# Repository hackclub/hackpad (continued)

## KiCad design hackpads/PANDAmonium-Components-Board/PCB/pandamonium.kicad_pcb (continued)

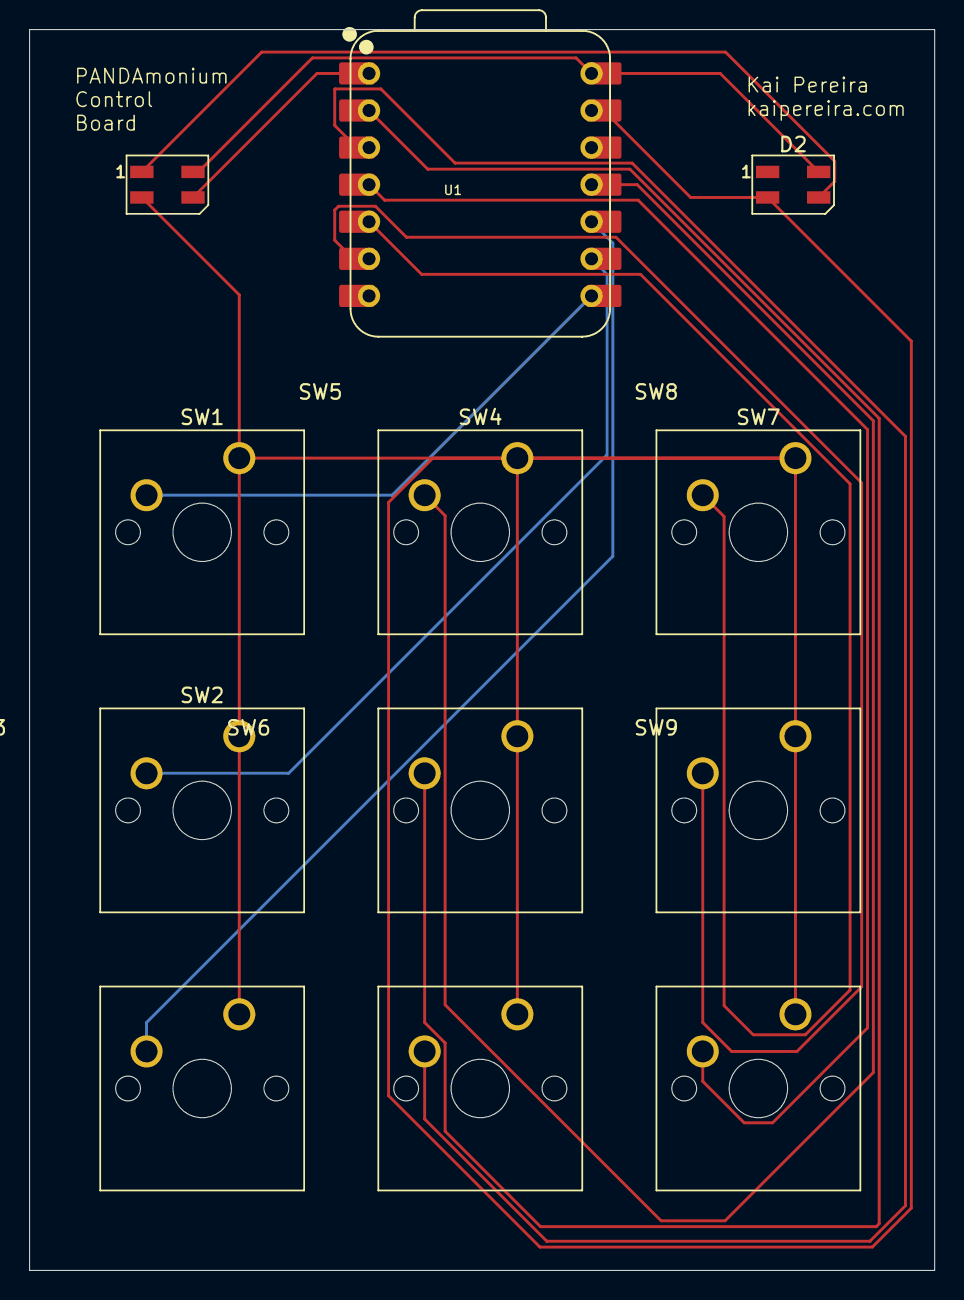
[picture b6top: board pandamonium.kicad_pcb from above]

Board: 2 copper layers, 62.0 x 85.0 mm, 12 parts (0 on the bottom side), 13 nets.

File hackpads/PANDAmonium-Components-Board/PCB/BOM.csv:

"Id";"Designator";"Footprint";"Quantity";"Designation";"Supplier and ref";
1;"SW6,SW9,SW1,SW4,SW7,SW2,SW5,SW3,SW8";"SW_Cherry_MX_1.00u_PCB";9;"SW_Push";;;
2;"D1,D2";"LED_SK6812MINI_PLCC4_3.5x3.5mm_P1.75mm";2;"SK6812MINI";;;
3;"U1";"XIAO-RP2040-DIP";1;"XIAO-RP2040-DIP";;;

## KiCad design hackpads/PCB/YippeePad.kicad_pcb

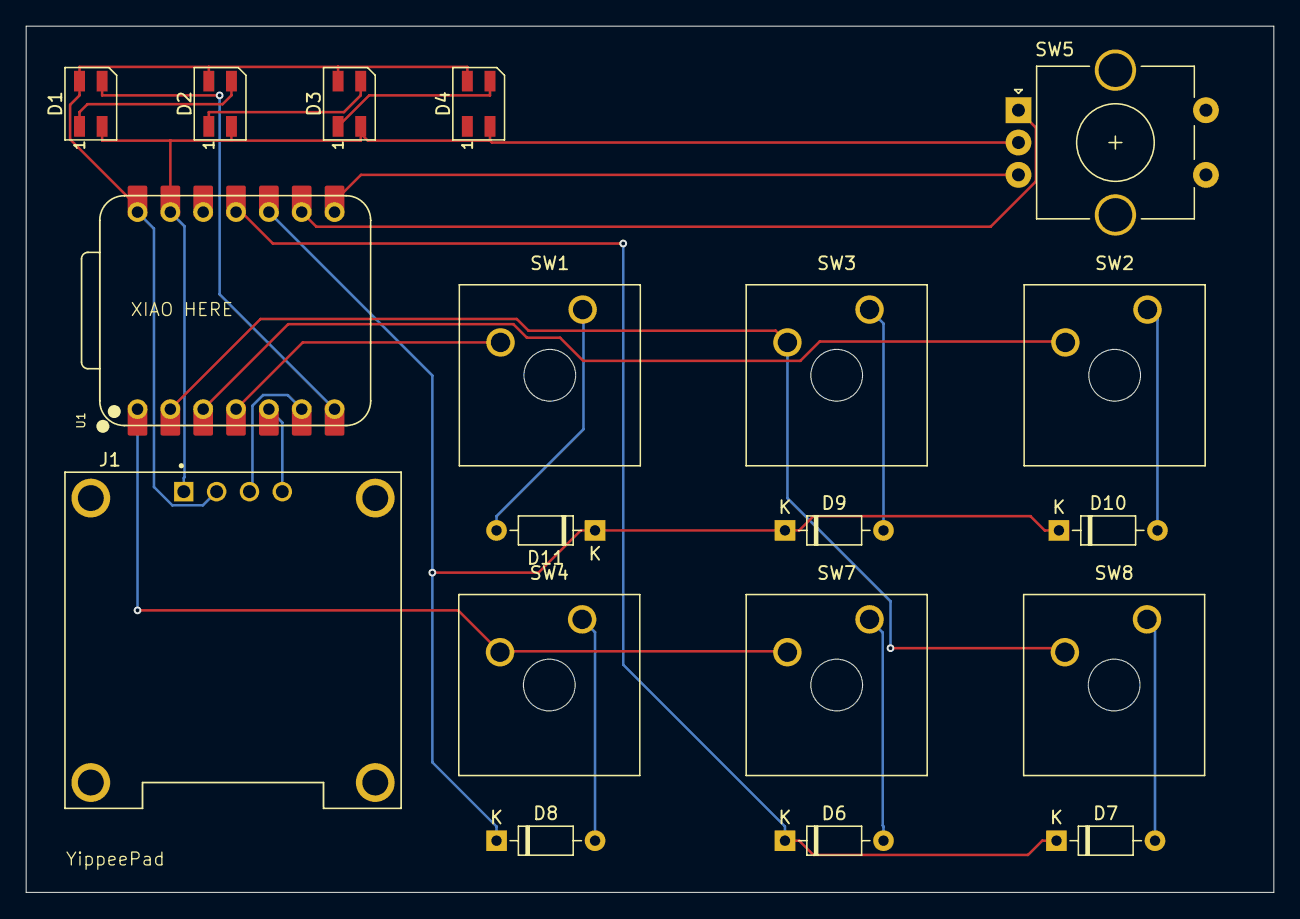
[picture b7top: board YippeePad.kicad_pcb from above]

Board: 2 copper layers, 96.5 x 67.0 mm, 19 parts (0 on the bottom side), 22 nets.

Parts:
D1, D2, D3, D4: SK6812MINI; LED_SK6812MINI_PLCC4_3.5x3.5mm_P1.75mm
D6, D7, D8, D9, D10, D11: 1N4148; D_DO-35_SOD27_P7.62mm_Horizontal
J1: Conn_01x04_Pin; MODULE_DM-OLED096-636_128x64
SW1, SW2, SW3, SW4, SW7, SW8: SW_Push; CherryMX_1.00u
SW5: RotaryEncoder; RotaryEncoder_Alps_EC11E-Switch_Vertical_H20mm_CircularMoun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
U1: XIAO-RP2040-DIP

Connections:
+5V: D1.4 (VDD), D2.4 (VDD), D3.4 (VDD), D4.4 (VDD), J1.2, U1.14 (VBUS)
Col 0: SW4.1, SW7.1, U1.1 (GPIO26/ADC0/A0)
Col 1: SW3.1, SW8.1, U1.2 (GPIO27/ADC1/A1)
Col 2: SW2.1, U1.3 (GPIO28/ADC2/A2)
Col 3: SW1.1, U1.4 (GPIO29/ADC3/A3)
GND: D1.2 (VSS), D2.2 (VSS), D3.2 (VSS), D4.2 (VSS), J1.1, SW5.C, U1.13 (GND)
unnamed: D1.3 (DIN), U1.7 (GPIO0/TX)
unnamed: D1.1 (DOUT), D2.3 (DIN)
unnamed: D2.1 (DOUT), D3.3 (DIN)
unnamed: D3.1 (DOUT), D4.3 (DIN)
unnamed: D6.2 (A), SW7.2
unnamed: D7.2 (A), SW8.2
unnamed: D8.2 (A), SW4.2
unnamed: D9.2 (A), SW3.2
unnamed: D10.2 (A), SW2.2
unnamed: D11.2 (A), SW1.2
unnamed: SW5.B, U1.8 (GPIO1/RX)
unnamed: SW5.A, U1.9 (GPIO2/SCK)
Row 0: D6.1 (K), D7.1 (K), U1.11 (GPIO3/MOSI)
Row 1: D8.1 (K), D9.1 (K), D10.1 (K), D11.1 (K), U1.10 (GPIO4/MISO)
SCL: J1.3, U1.6 (GPIO7/SCL)
SDA: J1.4, U1.5 (GPIO6/SDA)
